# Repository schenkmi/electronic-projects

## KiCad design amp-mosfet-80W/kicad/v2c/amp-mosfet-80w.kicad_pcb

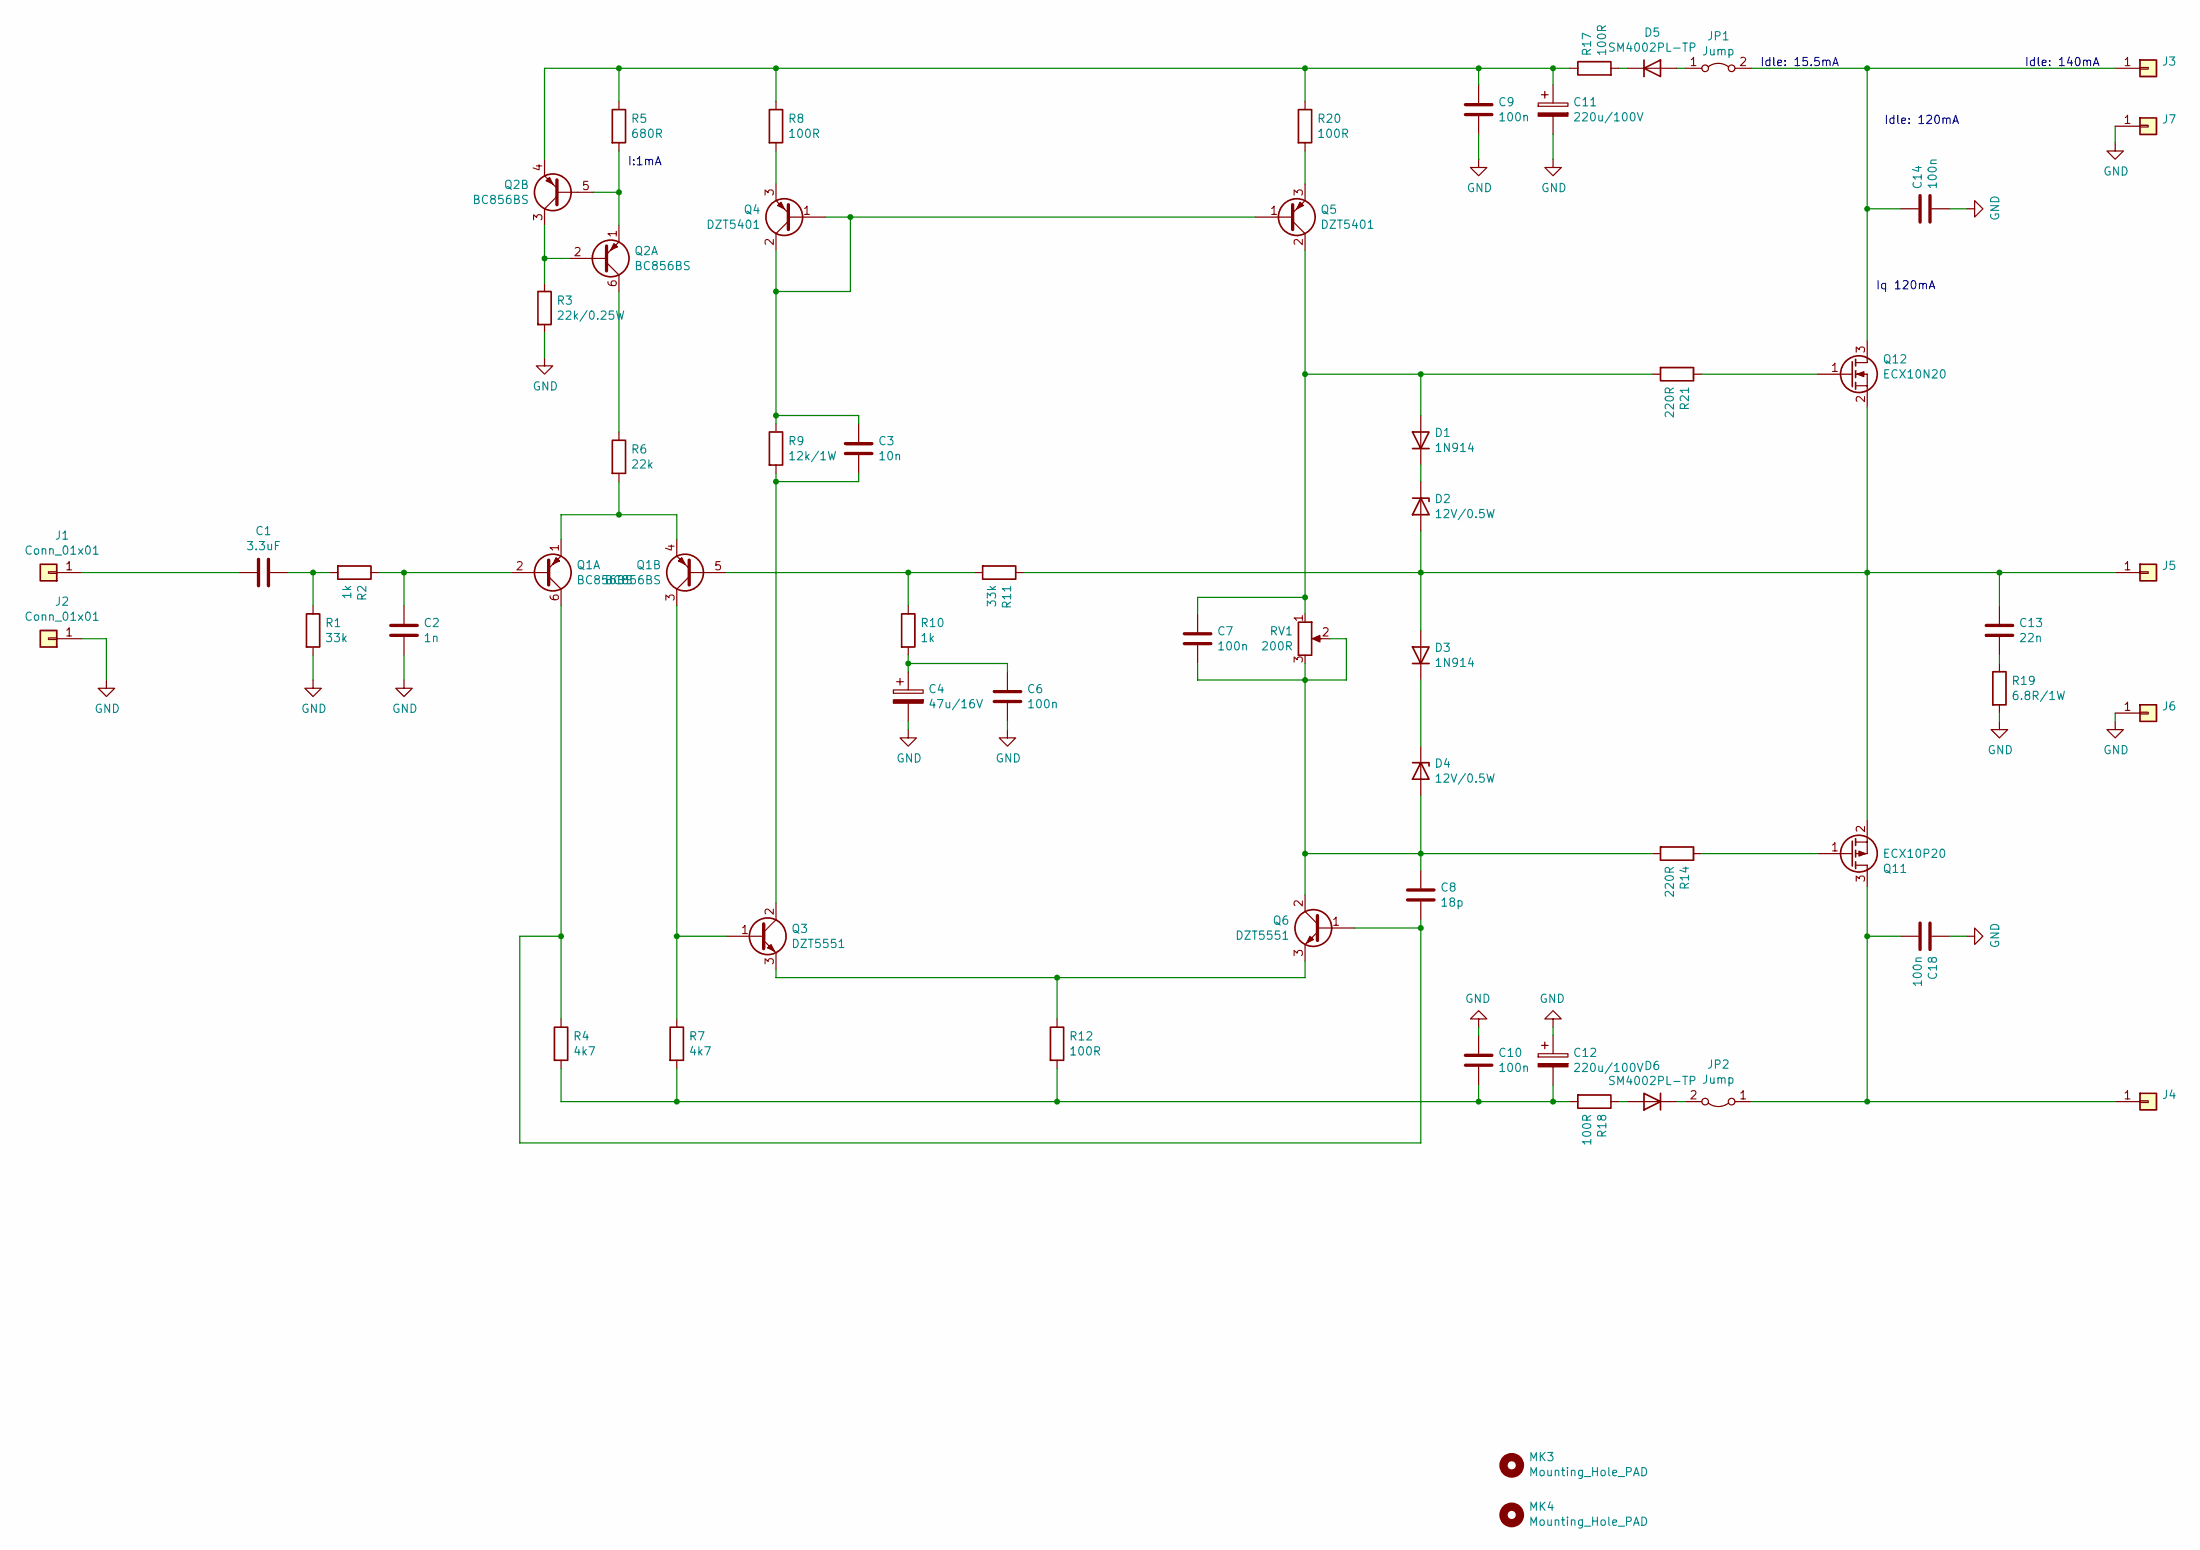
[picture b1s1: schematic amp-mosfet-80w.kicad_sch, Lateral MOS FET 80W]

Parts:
C1: 3.3uF; C_Rect_L7.2mm_W7.2mm_P5.00mm_FKS2_FKP2_MKS2_MKP2
C2: 1n; C_Rect_L7.2mm_W2.5mm_P5.00mm_FKS2_FKP2_MKS2_MKP2
C3: 10n; C_Rect_L7.2mm_W2.5mm_P5.00mm_FKS2_FKP2_MKS2_MKP2
C4: 47u/16V; CP_Radial_D5.0mm_P2.00mm
C6, C7, C9, C10, C14, C18: 100n; C_Rect_L7.2mm_W2.5mm_P5.00mm_FKS2_FKP2_MKS2_MKP2
C8: 18p; C_0805_2012Metric_Pad1.18x1.45mm_HandSolder
C11, C12: 220u/100V; CP_Radial_D12.5mm_P5.00mm
C13: 22n; C_Rect_L7.2mm_W2.5mm_P5.00mm_FKS2_FKP2_MKS2_MKP2
D1, D3: 1N914; D_SOD-123
D2, D4: 12V/0.5W; D_SOD-123
D5, D6: SM4002PL-TP; D_SOD-123F
J1, J2: Conn_01x01; Pin_D1.0mm_L10.0mm
J3, J4, J5, J6, J7: (no value)
JP1, JP2: Jump; PinHeader_1x02_P2.54mm_Vertical
MK3, MK4: Mounting_Hole_PAD; MountingHole_3.2mm_M3_Pad_Via
Q1, Q2: BC856BS; SOT-363_SC-70-6
Q3, Q6: DZT5551; SOT-223-3_TabPin2
Q4, Q5: DZT5401; SOT-223-3_TabPin2
Q11: ECX10P20; TO-247-3_Horizontal_TabUp
Q12: ECX10N20; TO-247-3_Horizontal_TabUp
R1, R11: 33k; R_0805_2012Metric_Pad1.20x1.40mm_HandSolder
R2, R10: 1k; R_0805_2012Metric_Pad1.20x1.40mm_HandSolder
R3: 22k/0.25W; R_0805_2012Metric_Pad1.20x1.40mm_HandSolder
R4, R7: 4k7; R_0805_2012Metric_Pad1.20x1.40mm_HandSolder
R5: 680R; R_0805_2012Metric_Pad1.20x1.40mm_HandSolder
R6: 22k; R_0805_2012Metric_Pad1.20x1.40mm_HandSolder
R8, R12, R17, R18, R20: 100R; R_0805_2012Metric_Pad1.20x1.40mm_HandSolder
R9: 12k/1W; R_1206_3216Metric_Pad1.30x1.75mm_HandSolder
R14, R21: 220R; R_0805_2012Metric_Pad1.20x1.40mm_HandSolder
R19: 6.8R/1W; R_MELF_MMB-0207
RV1: 200R; Potentiometer_Bourns_3296W_Vertical

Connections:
GND: C2.2, C4.2, C6.2, C9.2, C10.1, C11.2, C12.1, C14.2, C18.1, J2.1, J6.1, J7.1, R1.2, R3.2, R19.2
unnamed: C1.1, R1.1, R2.2
unnamed: C1.2, J1.1
unnamed: C2.1, Q1.2 (B1), R2.1
unnamed: C3.1, Q4.1 (B), Q4.2 (C), Q5.1 (B), R9.1
unnamed: C3.2, Q3.2 (C), R9.2
unnamed: C4.1, C6.1, R10.2
unnamed: C7.1, C8.2, D4.2 (A), Q6.2 (C), R14.2, RV1.2, RV1.3
unnamed: C7.2, D1.2 (A), Q5.2 (C), R21.2, RV1.1
unnamed: C8.1, Q1.6 (C1), Q6.1 (B), R4.1
unnamed: C10.2, C12.2, R4.2, R7.2, R12.2, R18.2
unnamed: C9.1, C11.1, Q2.4 (E2), R5.1, R8.1, R17.1, R20.1
unnamed: C13.1, D2.2 (A), D3.2 (A), J5.1, Q11.2 (D), Q12.2 (S), R11.1
unnamed: C13.2, R19.1
unnamed: C14.1, J3.1, JP1.2 (B), Q12.3 (D)
unnamed: C18.2, J4.1, JP2.1 (A), Q11.3 (S)
unnamed: D1.1 (K), D2.1 (K)
unnamed: D3.1 (K), D4.1 (K)
unnamed: D5.1 (K), R17.2
unnamed: D5.2 (A), JP1.1 (A)
unnamed: D6.1 (K), JP2.2 (B)
unnamed: D6.2 (A), R18.1
unnamed: Q1.1 (E1), Q1.4 (E2), R6.2
unnamed: Q1.3 (C2), Q3.1 (B), R7.1
unnamed: Q1.5 (B2), R10.1, R11.2
unnamed: Q2.1 (E1), Q2.5 (B2), R5.2
unnamed: Q2.2 (B1), Q2.3 (C2), R3.1
unnamed: Q2.6 (C1), R6.1
unnamed: Q3.3 (E), Q6.3 (E), R12.1
unnamed: Q4.3 (E), R8.2
unnamed: Q5.3 (E), R20.2
unnamed: Q11.1 (G), R14.1
unnamed: Q12.1 (G), R21.1

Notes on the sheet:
Idle: 120mA
Iq 120mA
Idle: 15.5mA
Idle: 140mA
I:1mA

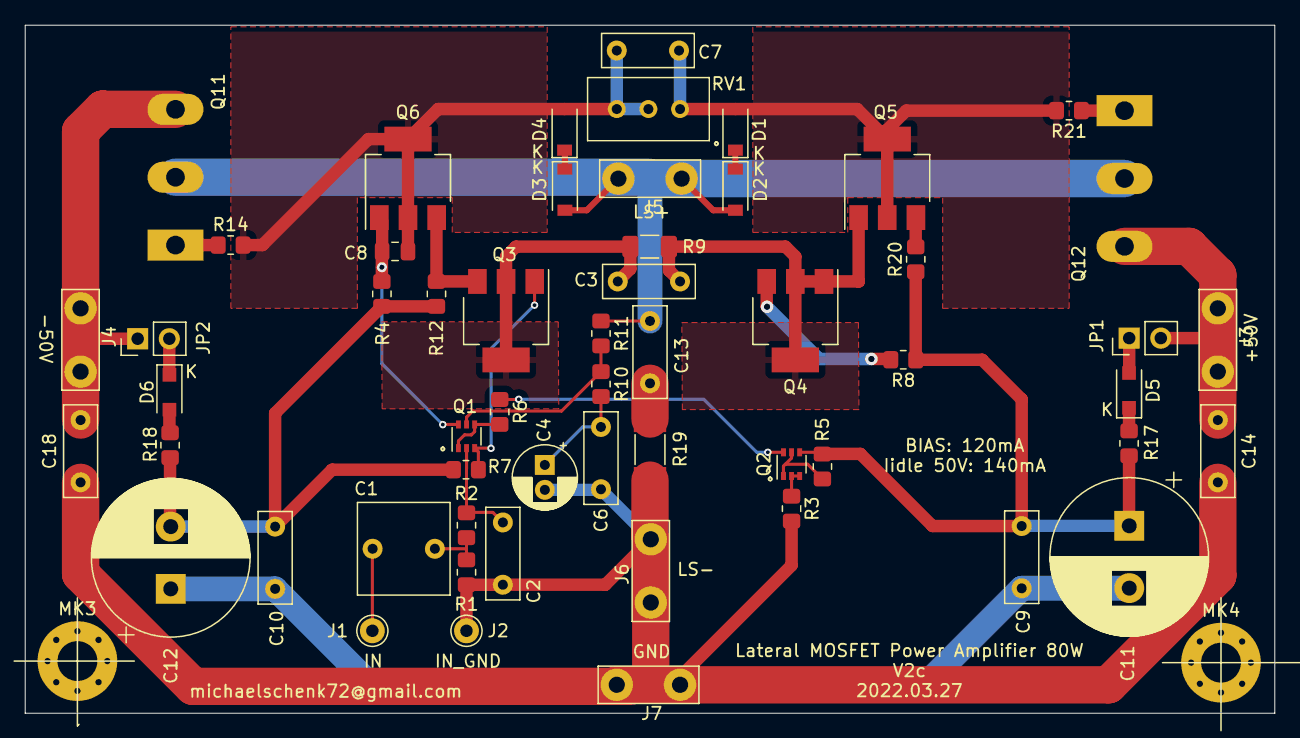
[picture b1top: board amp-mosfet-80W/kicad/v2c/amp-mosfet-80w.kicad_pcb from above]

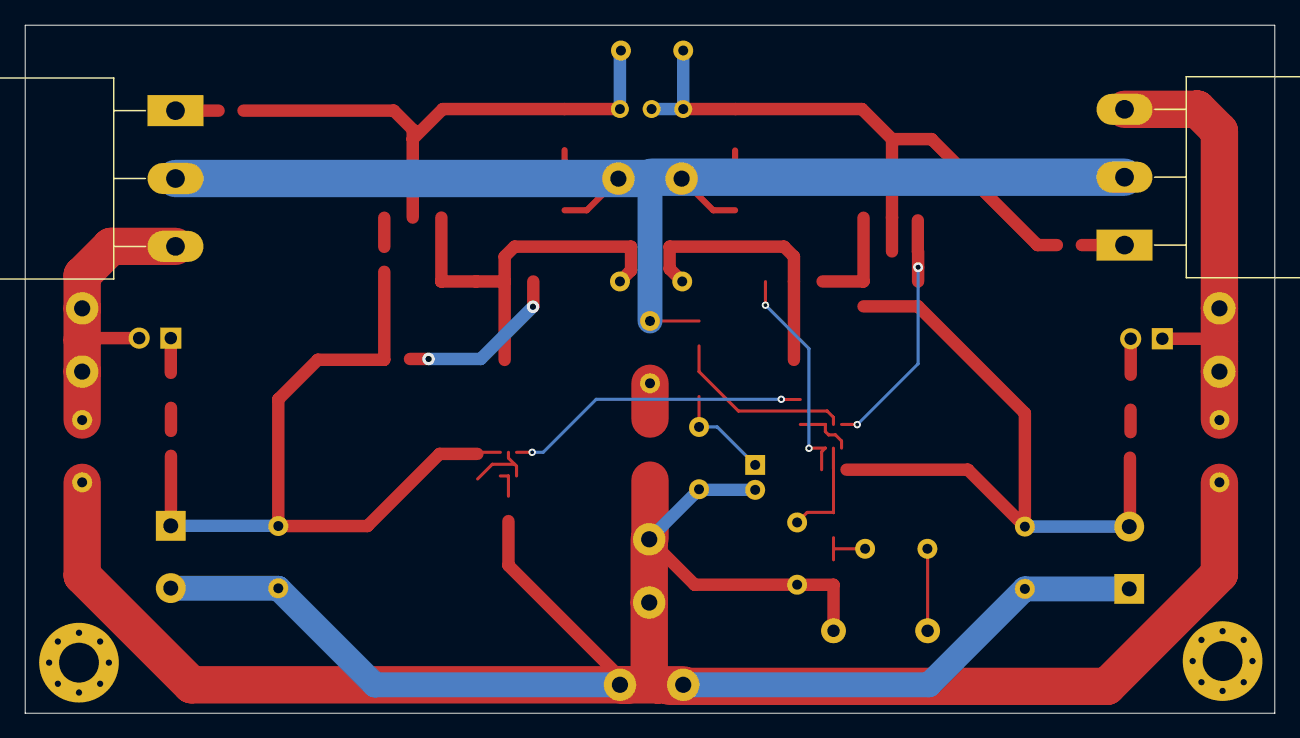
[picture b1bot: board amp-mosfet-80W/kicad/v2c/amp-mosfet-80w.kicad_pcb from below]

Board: 2 copper layers, 100.3 x 55.2 mm, 58 parts (2 on the bottom side), 33 nets.

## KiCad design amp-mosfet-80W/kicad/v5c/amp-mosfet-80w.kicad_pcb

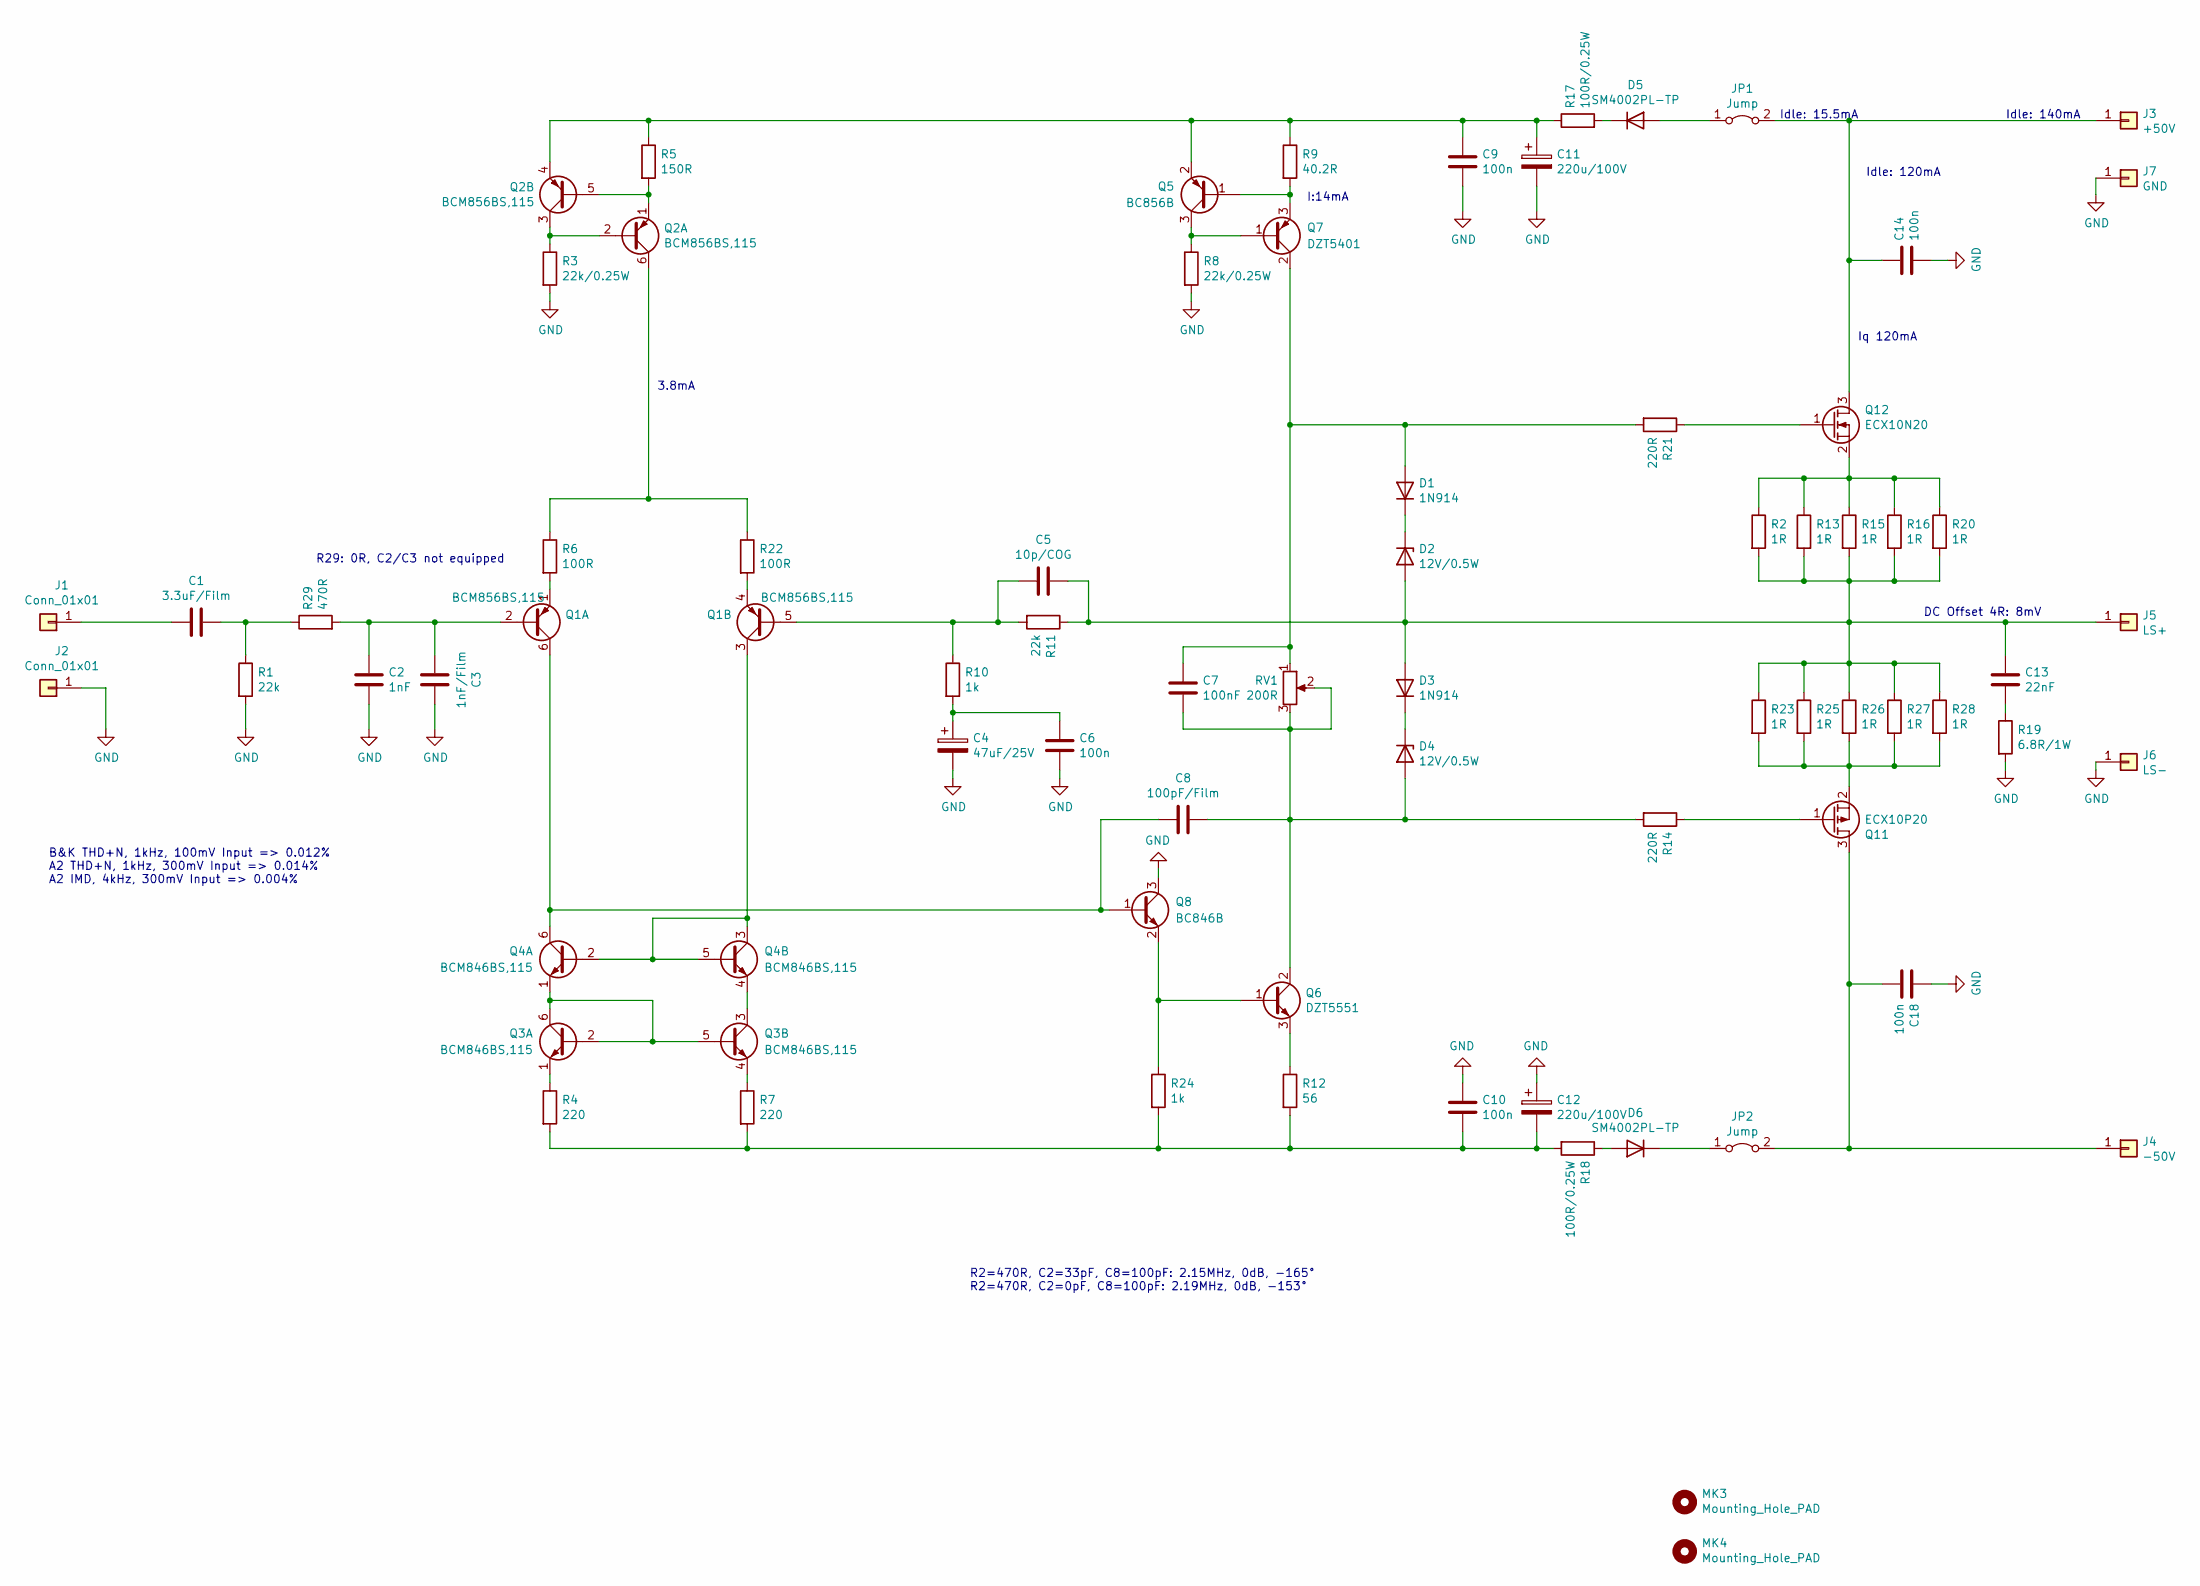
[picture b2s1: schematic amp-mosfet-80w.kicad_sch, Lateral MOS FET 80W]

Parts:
C1: 3.3uF/Film; C_Rect_L7.2mm_W7.2mm_P5.00mm_FKS2_FKP2_MKS2_MKP2
C2: 1nF; C_Rect_L7.2mm_W2.5mm_P5.00mm_FKS2_FKP2_MKS2_MKP2
C3: 1nF/Film; C_0805_2012Metric_Pad1.18x1.45mm_HandSolder
C4: 47uF/25V; CP_Radial_D5.0mm_P2.00mm
C5: 10p/COG; C_0805_2012Metric_Pad1.18x1.45mm_HandSolder
C6, C9, C10, C14, C18: 100n; C_Rect_L7.2mm_W2.5mm_P5.00mm_FKS2_FKP2_MKS2_MKP2
C7: 100nF; C_Rect_L7.2mm_W2.5mm_P5.00mm_FKS2_FKP2_MKS2_MKP2
C8: 100pF/Film; C_0805_2012Metric_Pad1.18x1.45mm_HandSolder
C11, C12: 220u/100V; CP_Radial_D12.5mm_P5.00mm
C13: 22nF; C_Rect_L7.2mm_W2.5mm_P5.00mm_FKS2_FKP2_MKS2_MKP2
D1, D3: 1N914; D_SOD-123
D2, D4: 12V/0.5W; D_SOD-123
D5, D6: SM4002PL-TP; D_SOD-123F
J1, J2: Conn_01x01; Pin_D1.0mm_L10.0mm
J3: +50V; TE-726386-2_Pitch5.08mm_Drill1.3mm
J4: -50V; TE-726386-2_Pitch5.08mm_Drill1.3mm
J5: LS+; TE-726386-2_Pitch5.08mm_Drill1.3mm
J6: LS-; TE-726386-2_Pitch5.08mm_Drill1.3mm
J7: GND; TE-726386-2_Pitch5.08mm_Drill1.3mm
JP1, JP2: Jump; PinHeader_1x02_P2.54mm_Vertical
MK3, MK4: Mounting_Hole_PAD; MountingHole_3.2mm_M3_Pad_Via
Q1, Q2: BCM856BS,115; SOT-363_SC-70-6
Q3, Q4: BCM846BS,115; SOT-363_SC-70-6
Q5: BC856B; SOT-23
Q6: DZT5551; SOT-223-3_TabPin2
Q7: DZT5401; SOT-223-3_TabPin2
Q8: BC846B; SOT-23
Q11: ECX10P20; TO-247-3_Horizontal_TabUp
Q12: ECX10N20; TO-247-3_Horizontal_TabUp
R1, R11: 22k; R_0805_2012Metric_Pad1.20x1.40mm_HandSolder
R2, R13, R15, R16, R20, R23, R25, R26, R27, R28: 1R; R_MELF_MMB-0207
R3, R8: 22k/0.25W; R_0805_2012Metric_Pad1.20x1.40mm_HandSolder
R4, R7: 220; R_0805_2012Metric_Pad1.20x1.40mm_HandSolder
R5: 150R; R_0805_2012Metric_Pad1.20x1.40mm_HandSolder
R6, R22: 100R; R_0805_2012Metric_Pad1.20x1.40mm_HandSolder
R9: 40.2R; R_0805_2012Metric_Pad1.20x1.40mm_HandSolder
R10, R24: 1k; R_0805_2012Metric_Pad1.20x1.40mm_HandSolder
R12: 56; R_0805_2012Metric_Pad1.20x1.40mm_HandSolder
R14, R21: 220R; R_0805_2012Metric_Pad1.20x1.40mm_HandSolder
R17, R18: 100R/0.25W; R_0805_2012Metric_Pad1.20x1.40mm_HandSolder
R19: 6.8R/1W; R_MELF_MMB-0207
R29: 470R; R_0805_2012Metric_Pad1.20x1.40mm_HandSolder
RV1: 200R; Potentiometer_Bourns_3296W_Vertical

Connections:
GND: C2.2, C3.1, C4.2, C6.2, C9.2, C10.1, C11.2, C12.1, C14.2, C18.1, J2.1, J6.1, J7.1, Q8.3 (C), R1.2, R3.2, R8.2, R19.2
unnamed: C1.1, R1.1, R29.1
unnamed: C1.2, J1.1
unnamed: C4.1, C6.1, R10.2
unnamed: C7.1, C8.1, D4.2 (A), Q6.2 (C), R14.2, RV1.2, RV1.3
unnamed: C7.2, D1.2 (A), Q7.2 (C), R21.2, RV1.1
unnamed: C8.2, Q1.6 (C1), Q4.6 (C1), Q8.1 (B)
unnamed: C10.2, C12.2, R4.2, R7.2, R12.2, R18.2, R24.2
unnamed: C9.1, C11.1, Q2.4 (E2), Q5.2 (E), R5.1, R9.1, R17.1
unnamed: C5.1, C13.1, D2.2 (A), D3.2 (A), J5.1, R2.2, R11.1, R13.2, R15.2, R16.2, R20.2, R23.1, R25.1, R26.1, R27.1, R28.1
unnamed: C13.2, R19.1
unnamed: C14.1, J3.1, JP1.2 (B), Q12.3 (D)
unnamed: C18.2, J4.1, JP2.2 (B), Q11.3 (S)
unnamed: D1.1 (K), D2.1 (K)
unnamed: D3.1 (K), D4.1 (K)
unnamed: D5.1 (K), R17.2
unnamed: D5.2 (A), JP1.1 (A)
unnamed: D6.1 (K), JP2.1 (A)
unnamed: D6.2 (A), R18.1
unnamed: Q1.1 (E1), R6.2
unnamed: C2.1, C3.2, Q1.2 (B1), R29.2
unnamed: Q1.3 (C2), Q4.2 (B1), Q4.3 (C2), Q4.5 (B2)
unnamed: Q1.4 (E2), R22.2
unnamed: C5.2, Q1.5 (B2), R10.1, R11.2
unnamed: Q2.1 (E1), Q2.5 (B2), R5.2
unnamed: Q2.2 (B1), Q2.3 (C2), R3.1
unnamed: Q2.6 (C1), R6.1, R22.1
unnamed: Q3.1 (E1), R4.1
unnamed: Q3.2 (B1), Q3.5 (B2), Q3.6 (C1), Q4.1 (E1)
unnamed: Q3.3 (C2), Q4.4 (E2)
unnamed: Q3.4 (E2), R7.1
unnamed: Q5.1 (B), Q7.3 (E), R9.2
unnamed: Q5.3 (C), Q7.1 (B), R8.1
unnamed: Q6.1 (B), Q8.2 (E), R24.1
unnamed: Q6.3 (E), R12.1
unnamed: Q11.1 (G), R14.1
unnamed: Q11.2 (D), R23.2, R25.2, R26.2, R27.2, R28.2
unnamed: Q12.1 (G), R21.1
unnamed: Q12.2 (S), R2.1, R13.1, R15.1, R16.1, R20.1

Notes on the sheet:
B&K THD+N, 1kHz, 100mV Input => 0.012% A2 THD+N, 1kHz, 300mV Input => 0.014% A2 IMD, 4kHz, 300mV Input => 0.004%
Idle: 120mA
Iq 120mA
Idle: 15.5mA
R2=470R, C2=33pF, C8=100pF: 2.15MHz, 0dB, -165° R2=470R, C2=0pF, C8=100pF: 2.19MHz, 0dB, -153°
Idle: 140mA
DC Offset 4R: 8mV
R29: 0R, C2/C3 not equipped
3.8mA
I:14mA

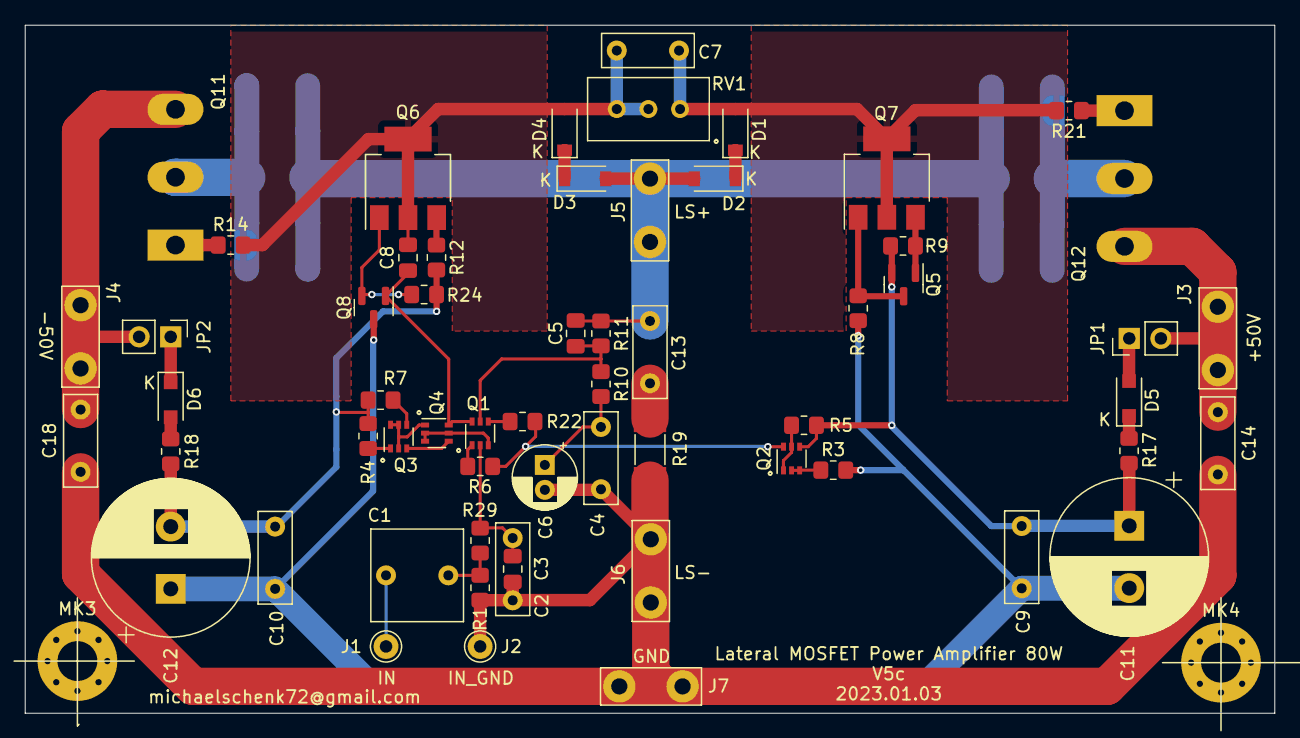
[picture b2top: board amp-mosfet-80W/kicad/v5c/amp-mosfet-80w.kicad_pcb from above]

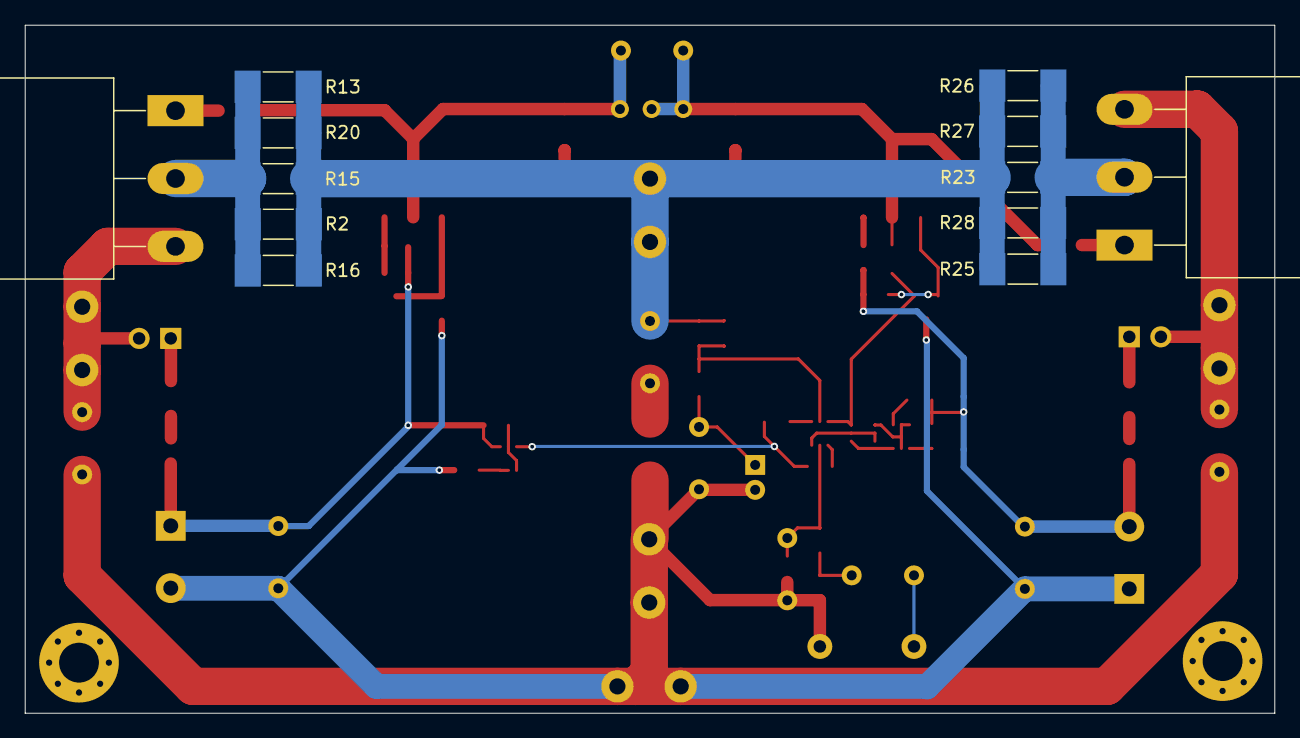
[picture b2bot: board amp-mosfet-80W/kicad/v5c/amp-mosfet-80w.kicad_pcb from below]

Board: 2 copper layers, 100.3 x 55.2 mm, 72 parts (12 on the bottom side), 39 nets.
